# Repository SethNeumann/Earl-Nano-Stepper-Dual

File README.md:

# REPO NAME: Earl-Nano-Stepper-Dual

## License: Creative Commons Attribution-NonCommercial-ShareAlike

This is a revision of Earls-Nano-Stepper which supported a single stepper motor with an Arduino Nano, a ULN2003 high current driver, a molex connector
for the stepper and inputs for home sensors.  This version uses a ULN2803 with 8 segments to support 2 steppers (4 ea), 2 molex connectors and 2 home sensors.

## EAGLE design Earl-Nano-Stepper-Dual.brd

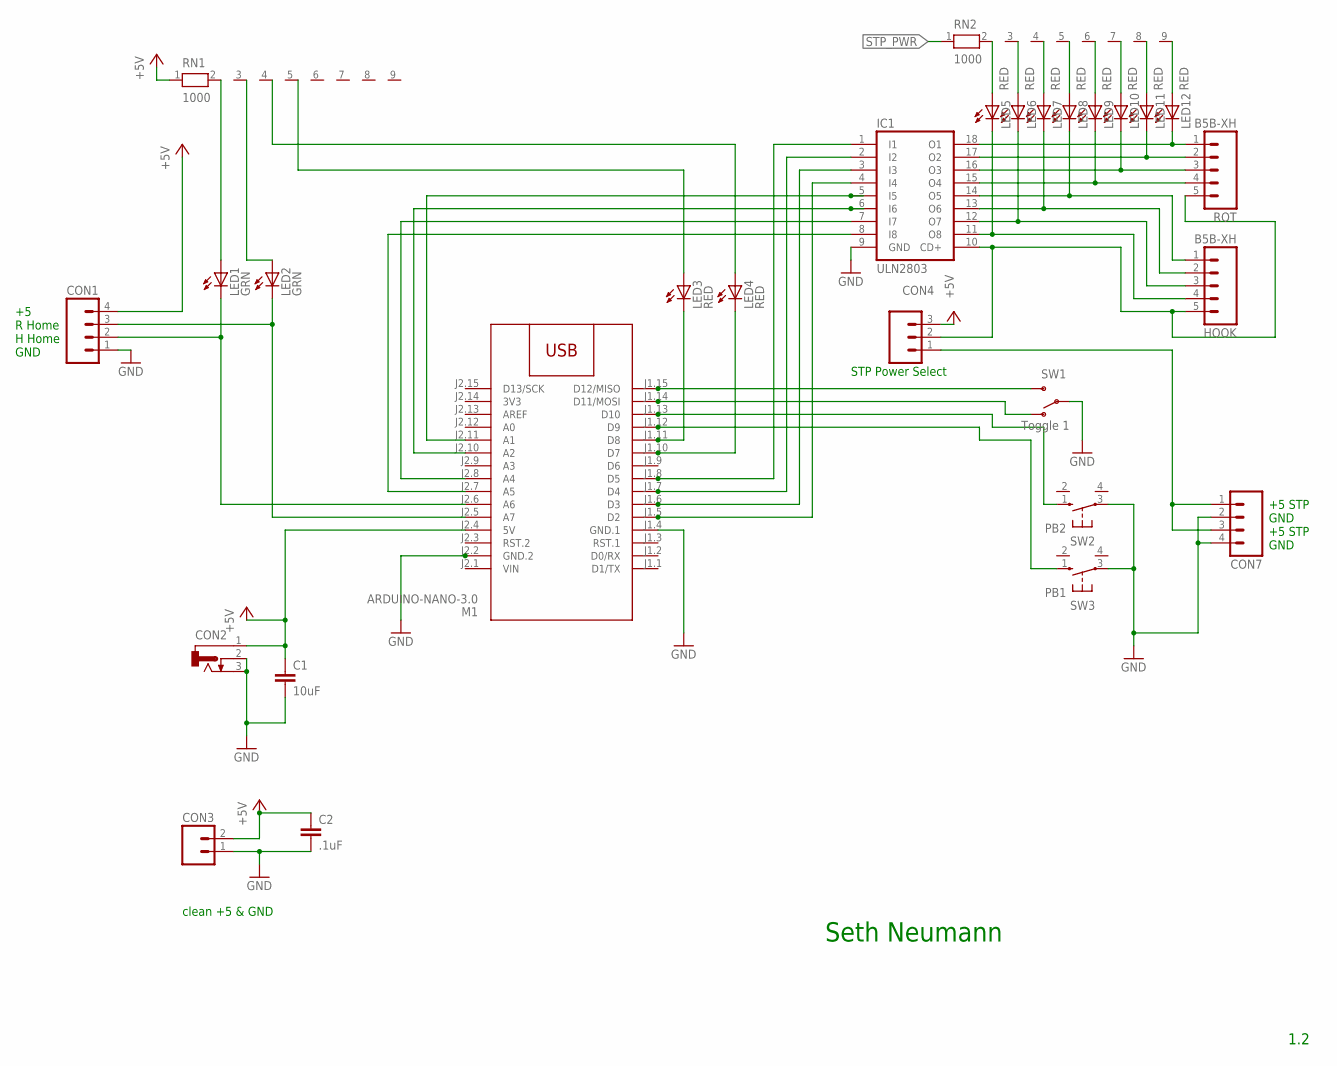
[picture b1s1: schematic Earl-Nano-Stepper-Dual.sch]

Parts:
C1: 10uF; C5B3
C2: .1uF; C5B3
CON1: CONNECTOR-M04LOCK; 1X04_LOCK
CON2: CONNECTOR-DC-POWER-RA; DCJ0202
CON3: CONNECTOR-M02350-LOCK; 1751248
CON4: CONNECTOR-M03254-LOCK; 3POL254
CON7: CONNECTOR-M04SCREW_LOCK; SCREWTERMINAL-3.5MM-4_LOCK
HOOK: B5B-XH; 1X05_LOCK
IC1: ULN2803; DIL18
LED1, LED2: GRN; LED3MM
LED3, LED4, LED5, LED6, LED7, LED8, LED9, LED10, LED11, LED12: RED; LED3MM
M1: ARDUINO-NANO-3.0
RN1, RN2: 1000; RN-9
ROT: B5B-XH; 1X05_LOCK
SW1: Toggle 1; SWITCH-SPDT-508
SW2: PB2; 4P-PTH-6.0X6.0X5.0H
SW3: PB1; 4P-PTH-6.0X6.0X5.0H

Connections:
3V3: M1.J2.14 (3V3)
+5V: C1.1, C2.1, CON1.4, CON2.1, CON3.2 (B), CON4.3, M1.J2.4 (5V), RN1.1
GND: C1.2, C2.2, CON1.1, CON2.2, CON2.3, CON3.1 (A), CON7.2, CON7.4, IC1.9 (GND), M1.J1.4 (GND.1), M1.J2.2 (GND.2), SW1.2, SW2.3, SW3.3
unnamed: IC1.18 (O1), LED12.K (C), ROT.1
unnamed: M1.J1.15 (D12/MISO), SW1.3 (S)
unnamed: M1.J1.14 (D11/MOSI), SW1.1 (O)
unnamed: M1.J1.13 (D10), SW2.1 (S)
unnamed: M1.J1.12 (D9), SW3.1 (S)
unnamed: LED3.K (C), M1.J1.11 (D8)
unnamed: LED4.K (C), M1.J1.10 (D7)
unnamed: LED3.A, RN1.5
unnamed: LED4.A, RN1.4
unnamed: LED2.A, RN1.3
unnamed: IC1.1 (I1), M1.J1.8 (D5)
unnamed: IC1.2 (I2), M1.J1.7 (D4)
unnamed: IC1.3 (I3), M1.J1.6 (D3)
unnamed: IC1.4 (I4), M1.J1.5 (D2)
unnamed: IC1.17 (O2), LED11.K (C), ROT.2
unnamed: IC1.16 (O3), LED10.K (C), ROT.3
unnamed: IC1.15 (O4), LED9.K (C), ROT.4
unnamed: LED9.A, RN2.6
unnamed: CON1.3, LED2.K (C), M1.J2.5 (A7)
unnamed: LED10.A, RN2.7
unnamed: LED11.A, RN2.8
unnamed: LED12.A, RN2.9
unnamed: IC1.5 (I5), M1.J2.11 (A1)
unnamed: IC1.6 (I6), M1.J2.10 (A2)
unnamed: IC1.7 (I7), M1.J2.8 (A4)
unnamed: IC1.8 (I8), M1.J2.7 (A5)
unnamed: LED5.A, RN2.2
unnamed: CON4.1, CON7.1, CON7.3
unnamed: CON1.2, LED1.K (C), M1.J2.6 (A6)
unnamed: LED1.A, RN1.2
unnamed: LED6.A, RN2.3
unnamed: HOOK.1, IC1.14 (O5), LED8.K (C)
unnamed: HOOK.2, IC1.13 (O6), LED7.K (C)
unnamed: HOOK.3, IC1.12 (O7), LED6.K (C)
unnamed: HOOK.4, IC1.11 (O8), LED5.K (C)
unnamed: LED7.A, RN2.4
unnamed: LED8.A, RN2.5
STP_PWR: CON4.2, HOOK.5, IC1.10 (CD+), RN2.1, ROT.5
VIN: M1.J2.1 (VIN)

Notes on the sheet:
Seth Neumann
1.2
clean +5 & GND
+5 STP GND +5 STP GND
STP Power Select
+5 R Home H Home GND

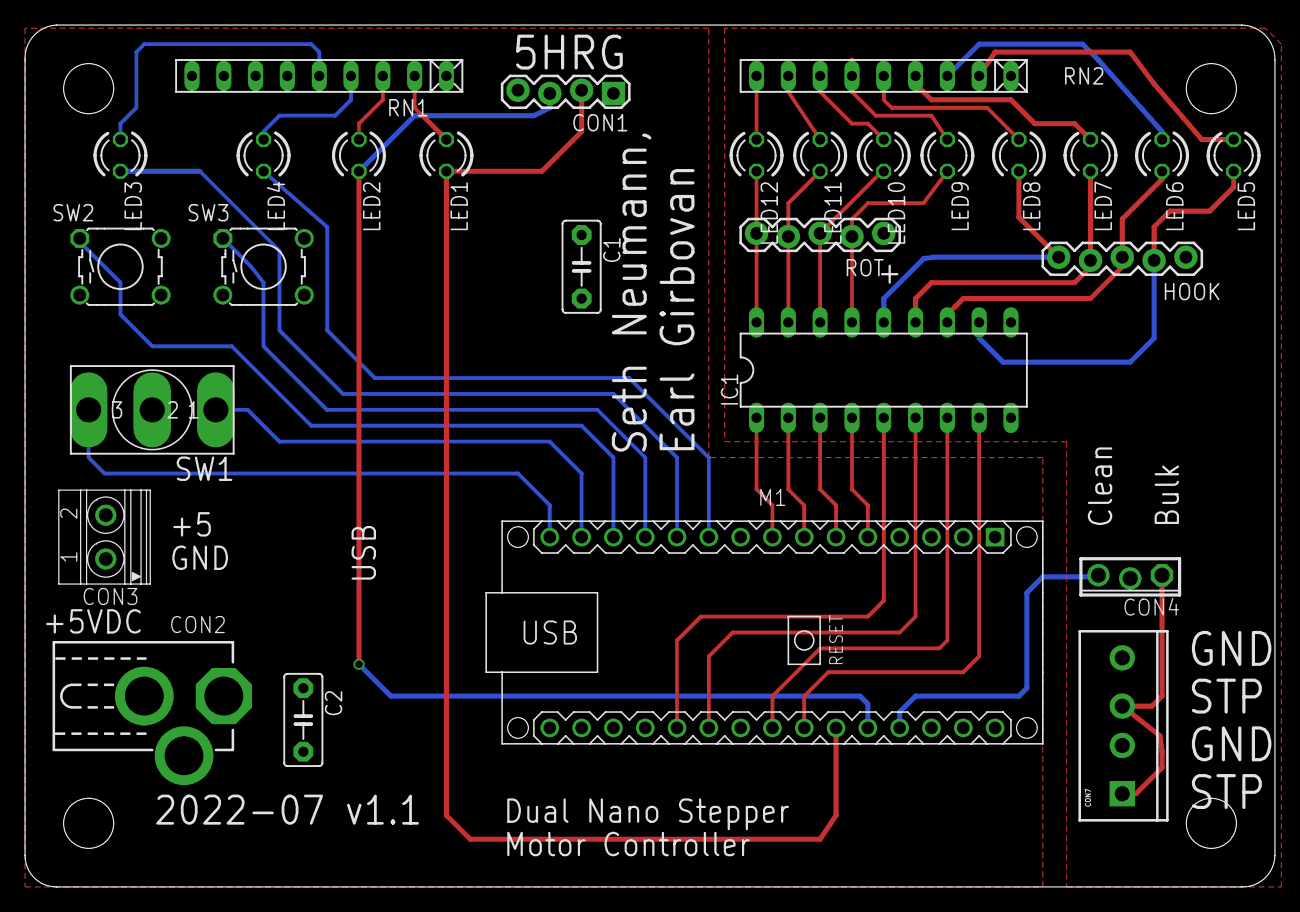
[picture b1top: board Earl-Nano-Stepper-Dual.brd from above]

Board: 2 copper layers, 99.8 x 68.8 mm, 32 parts (0 on the bottom side), 40 nets.

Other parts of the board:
U$1: BOARD-DINRAIL-2.71IN-MRCS
U$2: CA-PROP65WARNING
U$3: MRCSLOGOTOP
U$4: MRCSLOGOBTM

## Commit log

2022-07-04 Moved a copy of Earl's Nano Stepper into the repository
    just getting started
2022-07-05 changes to support two stepper motors
    changed to ULN2803
    Moved both home sensors to A6,A7
    Added LEDs, 2nd connector etc
2022-07-05 changes resulting initial board order
    changes resulting in initial board order
2022-07-05 changes for initial order
    changes to single stepper board to make a dual
2023-09-03 Documentation for Product Page
    created png and pdfs for schematic, layout and BOM
2023-09-03 Delete Earl-Nano-Stepper-Dual-Layout.pdf
    removed in favor of updated png

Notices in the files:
parts and their libraries:
diy-modules: Released under the Creative Commons Attribution 4.0 International License: http://creativecommons.org/licenses/by/4.0
